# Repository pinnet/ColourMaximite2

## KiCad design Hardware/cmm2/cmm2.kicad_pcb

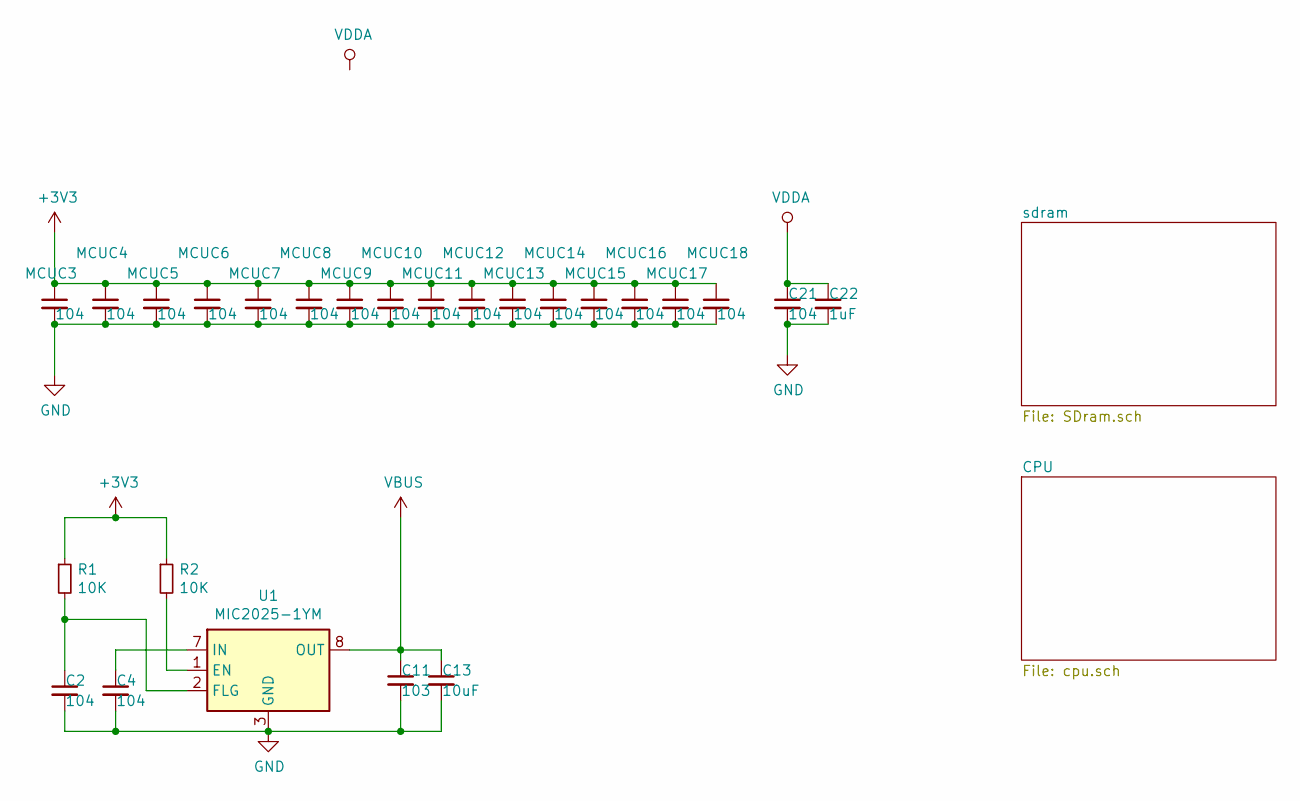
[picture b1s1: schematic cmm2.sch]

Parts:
C2, C4, C21: 104; C_0402_1005Metric
C11: 103; C_0402_1005Metric
C13: 10uF; C_0603_1608Metric
C22: 1uF; C_0402_1005Metric
MCUC3, MCUC4, MCUC5, MCUC6, MCUC7, MCUC8, MCUC9, MCUC10, MCUC11, MCUC12, MCUC13, MCUC14, MCUC15, MCUC16, MCUC17, MCUC18: 104; C_0402_1005Metric
R1, R2: 10K; R_0402_1005Metric
U1: MIC2025-1YM; SOIC-8_3.9x4.9mm_P1.27mm

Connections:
+3V3: MCUC3.1, MCUC4.1, MCUC5.1, MCUC6.1, MCUC7.1, MCUC8.1, MCUC9.1, MCUC10.1, MCUC11.1, MCUC12.1, MCUC13.1, MCUC14.1, MCUC15.1, MCUC16.1, MCUC17.1, MCUC18.1, R1.1, R2.1; also elsewhere on the board
GND: C2.2, C4.2, C11.2, C13.2, C21.2, C22.2, MCUC3.2, MCUC4.2, MCUC5.2, MCUC6.2, MCUC7.2, MCUC8.2, MCUC9.2, MCUC10.2, MCUC11.2, MCUC12.2, MCUC13.2, MCUC14.2, MCUC15.2, MCUC16.2, MCUC17.2, MCUC18.2, U1.3 (GND); also elsewhere on the board
unnamed: C2.1, R1.2, U1.2 (FLG)
unnamed: C4.1, U1.7 (IN)
unnamed: R2.2, U1.1 (EN)
VBUS: C11.1, C13.1, U1.6 (OUT), U1.8 (OUT)
VDDA: C21.1, C22.1; also elsewhere on the board

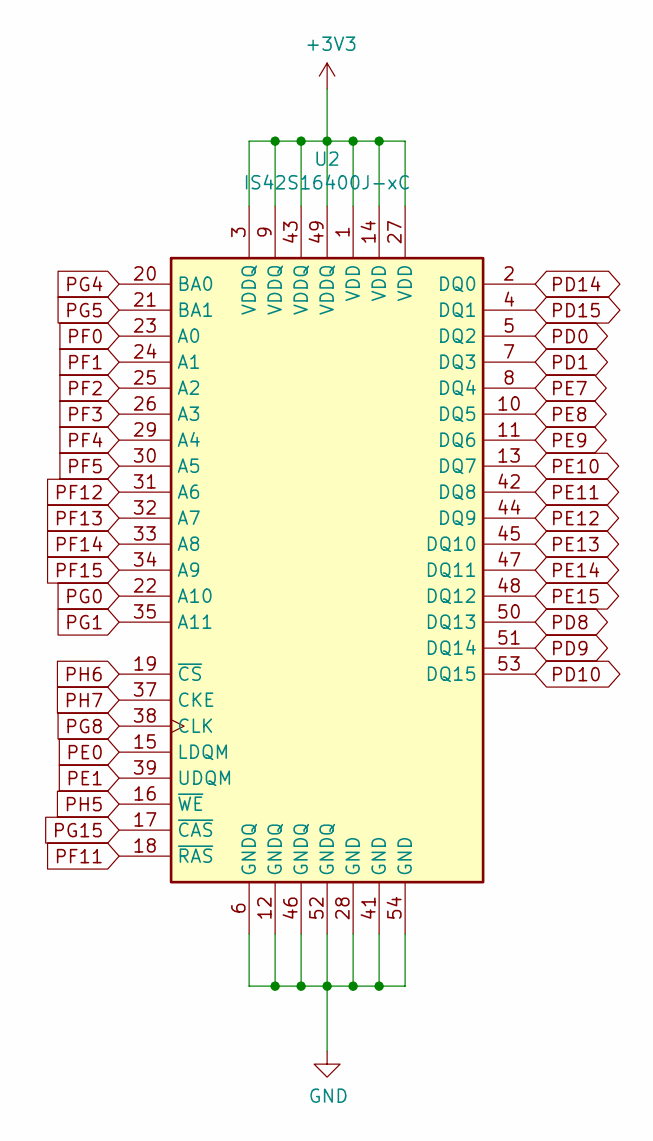
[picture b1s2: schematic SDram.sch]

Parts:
U2: IS42S16400J-xC; TSOP-II-54_22.2x10.16mm_P0.8mm

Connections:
+3V3: U2.1 (VDD), U2.3 (VDDQ), U2.9 (VDDQ), U2.14 (VDD), U2.27 (VDD), U2.43 (VDDQ), U2.49 (VDDQ); also elsewhere on the board
GND: U2.6 (GNDQ), U2.12 (GNDQ), U2.28 (GND), U2.41 (GND), U2.46 (GNDQ), U2.52 (GNDQ), U2.54 (GND); also elsewhere on the board
PD0: U2.5 (DQ2); also elsewhere on the board
PD1: U2.7 (DQ3); also elsewhere on the board
PD8: U2.50 (DQ13); also elsewhere on the board
PD9: U2.51 (DQ14); also elsewhere on the board
PD10: U2.53 (DQ15); also elsewhere on the board
PD14: U2.2 (DQ0); also elsewhere on the board
PD15: U2.4 (DQ1); also elsewhere on the board
PE0: U2.15 (LDQM); also elsewhere on the board
PE1: U2.39 (UDQM); also elsewhere on the board
PE7: U2.8 (DQ4); also elsewhere on the board
PE8: U2.10 (DQ5); also elsewhere on the board
PE9: U2.11 (DQ6); also elsewhere on the board
PE10: U2.13 (DQ7); also elsewhere on the board
PE11: U2.42 (DQ8); also elsewhere on the board
PE12: U2.44 (DQ9); also elsewhere on the board
PE13: U2.45 (DQ10); also elsewhere on the board
PE14: U2.47 (DQ11); also elsewhere on the board
PE15: U2.48 (DQ12); also elsewhere on the board
PF0: U2.23 (A0); also elsewhere on the board
PF1: U2.24 (A1); also elsewhere on the board
PF2: U2.25 (A2); also elsewhere on the board
PF3: U2.26 (A3); also elsewhere on the board
PF4: U2.29 (A4); also elsewhere on the board
PF5: U2.30 (A5); also elsewhere on the board
PF11: U2.18 (~RAS); also elsewhere on the board
PF12: U2.31 (A6); also elsewhere on the board
PF13: U2.32 (A7); also elsewhere on the board
PF14: U2.33 (A8); also elsewhere on the board
PF15: U2.34 (A9); also elsewhere on the board
PG0: U2.22 (A10); also elsewhere on the board
PG1: U2.35 (A11); also elsewhere on the board
PG4: U2.20 (BA0); also elsewhere on the board
PG5: U2.21 (BA1); also elsewhere on the board
PG8: U2.38 (CLK); also elsewhere on the board
PG15: U2.17 (~CAS); also elsewhere on the board
PH5: U2.16 (~WE); also elsewhere on the board
PH6: U2.19 (~CS); also elsewhere on the board
PH7: U2.37 (CKE); also elsewhere on the board

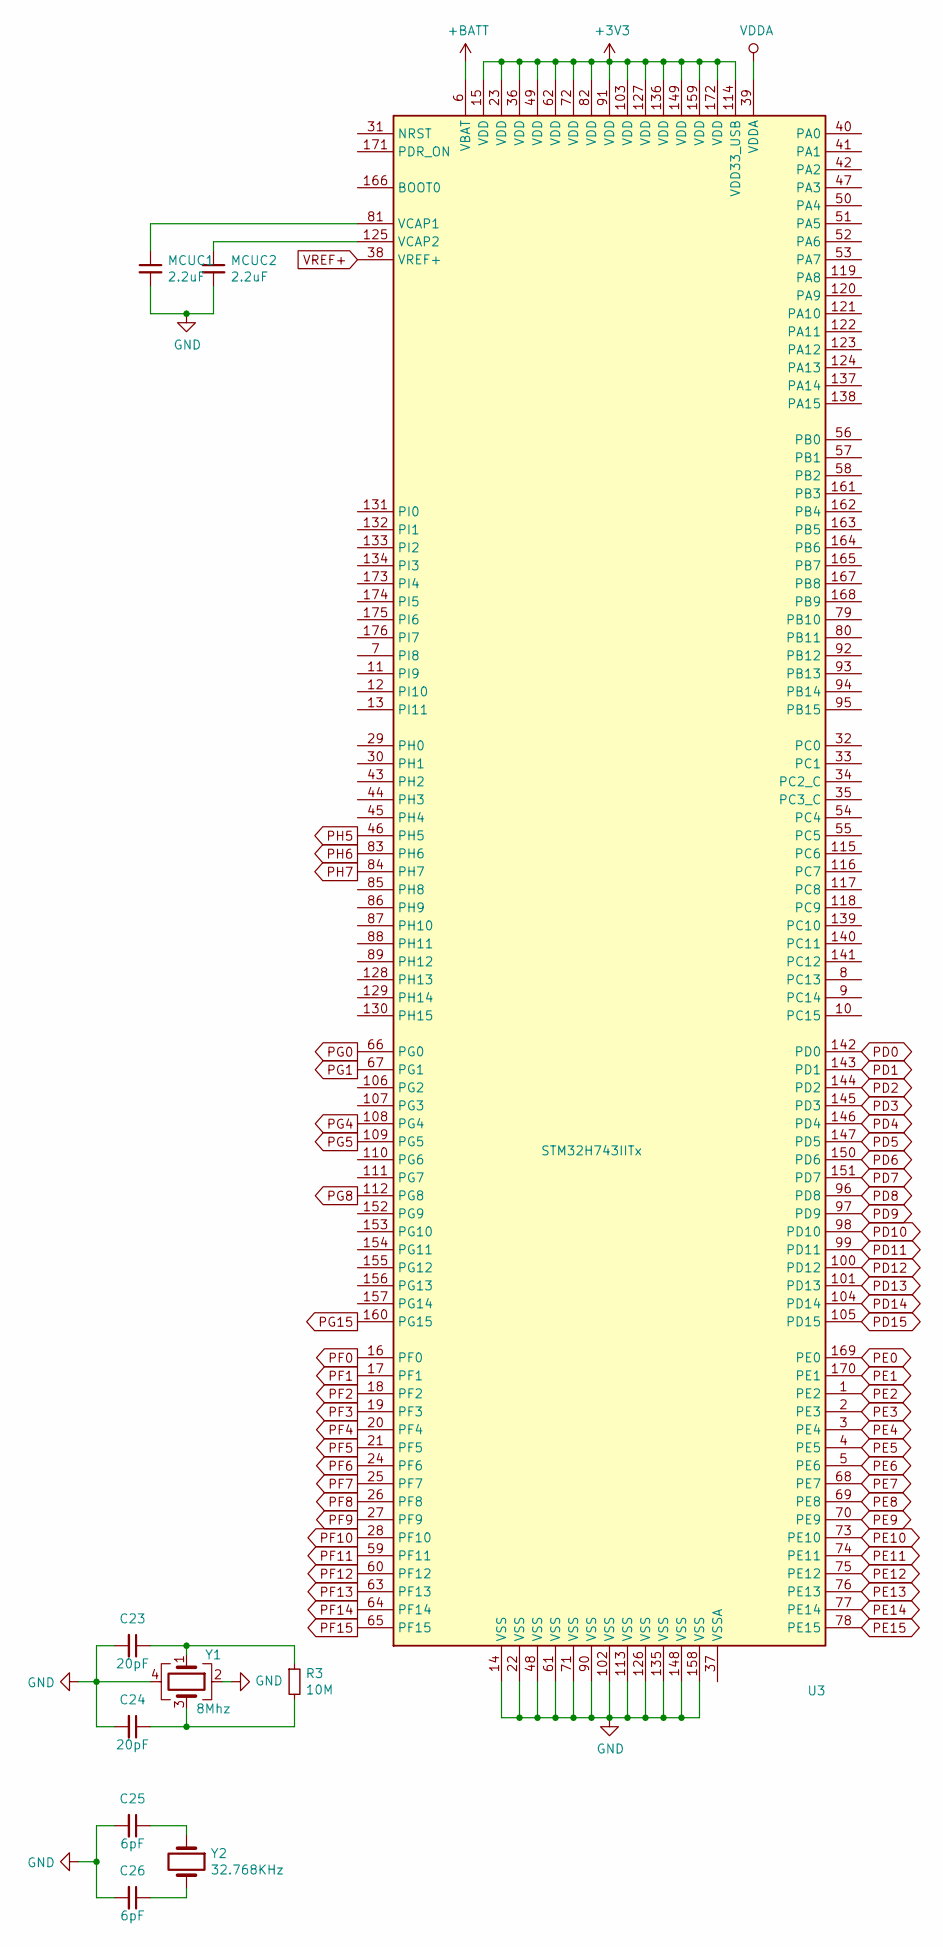
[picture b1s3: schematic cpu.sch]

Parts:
C23, C24: 20pF; C_0402_1005Metric
C25, C26: 6pF; C_0402_1005Metric
MCUC1, MCUC2: 2.2uF; C_0402_1005Metric
R3: 10M; R_0402_1005Metric
U3: STM32H743IITx; LQFP-176_24x24mm_P0.5mm
Y1: 8Mhz; Crystal_SMD_5032-4Pin_5.0x3.2mm
Y2: 32.768KHz; Crystal_SMD_3215-2Pin_3.2x1.5mm

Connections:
+3V3: U3.15 (VDD), U3.23 (VDD), U3.36 (VDD), U3.49 (VDD), U3.62 (VDD), U3.72 (VDD), U3.82 (VDD), U3.91 (VDD), U3.103 (VDD), U3.114 (VDD33_USB), U3.127 (VDD), U3.136 (VDD), U3.149 (VDD), U3.159 (VDD), U3.172 (VDD); also elsewhere on the board
+BATT: U3.6 (VBAT)
GND: C23.2, C24.2, C25.2, C26.2, MCUC1.2, MCUC2.2, U3.14 (VSS), U3.22 (VSS), U3.48 (VSS), U3.61 (VSS), U3.71 (VSS), U3.90 (VSS), U3.102 (VSS), U3.113 (VSS), U3.126 (VSS), U3.135 (VSS), U3.148 (VSS), U3.158 (VSS), Y1.2, Y1.4; also elsewhere on the board
unnamed: C23.1, R3.1, Y1.1
unnamed: C24.1, R3.2, Y1.3
unnamed: C25.1, Y2.1
unnamed: C26.1, Y2.2
unnamed: MCUC1.1, U3.81 (VCAP1)
unnamed: MCUC2.1, U3.125 (VCAP2)
PD0: U3.142 (PD0); also elsewhere on the board
PD1: U3.143 (PD1); also elsewhere on the board
PD2: U3.144 (PD2)
PD3: U3.145 (PD3)
PD4: U3.146 (PD4)
PD5: U3.147 (PD5)
PD6: U3.150 (PD6)
PD7: U3.151 (PD7)
PD8: U3.96 (PD8); also elsewhere on the board
PD9: U3.97 (PD9); also elsewhere on the board
PD10: U3.98 (PD10); also elsewhere on the board
PD11: U3.99 (PD11)
PD12: U3.100 (PD12)
PD13: U3.101 (PD13)
PD14: U3.104 (PD14); also elsewhere on the board
PD15: U3.105 (PD15); also elsewhere on the board
PE0: U3.169 (PE0); also elsewhere on the board
PE1: U3.170 (PE1); also elsewhere on the board
PE2: U3.1 (PE2)
PE3: U3.2 (PE3)
PE4: U3.3 (PE4)
PE5: U3.4 (PE5)
PE6: U3.5 (PE6)
PE7: U3.68 (PE7); also elsewhere on the board
PE8: U3.69 (PE8); also elsewhere on the board
PE9: U3.70 (PE9); also elsewhere on the board
PE10: U3.73 (PE10); also elsewhere on the board
PE11: U3.74 (PE11); also elsewhere on the board
PE12: U3.75 (PE12); also elsewhere on the board
PE13: U3.76 (PE13); also elsewhere on the board
PE14: U3.77 (PE14); also elsewhere on the board
PE15: U3.78 (PE15); also elsewhere on the board
PF0: U3.16 (PF0); also elsewhere on the board
PF1: U3.17 (PF1); also elsewhere on the board
PF2: U3.18 (PF2); also elsewhere on the board
PF3: U3.19 (PF3); also elsewhere on the board
PF4: U3.20 (PF4); also elsewhere on the board
PF5: U3.21 (PF5); also elsewhere on the board
PF6: U3.24 (PF6)
PF7: U3.25 (PF7)
PF8: U3.26 (PF8)
PF9: U3.27 (PF9)
PF10: U3.28 (PF10)
PF11: U3.59 (PF11); also elsewhere on the board
PF12: U3.60 (PF12); also elsewhere on the board
PF13: U3.63 (PF13); also elsewhere on the board
PF14: U3.64 (PF14); also elsewhere on the board
PF15: U3.65 (PF15); also elsewhere on the board
PG0: U3.66 (PG0); also elsewhere on the board
PG1: U3.67 (PG1); also elsewhere on the board
PG4: U3.108 (PG4); also elsewhere on the board
PG5: U3.109 (PG5); also elsewhere on the board
PG8: U3.112 (PG8); also elsewhere on the board
PG15: U3.160 (PG15); also elsewhere on the board
PH5: U3.46 (PH5); also elsewhere on the board
PH6: U3.83 (PH6); also elsewhere on the board
PH7: U3.84 (PH7); also elsewhere on the board
VDDA: U3.39 (VDDA); also elsewhere on the board
VREF+: U3.38 (VREF+)

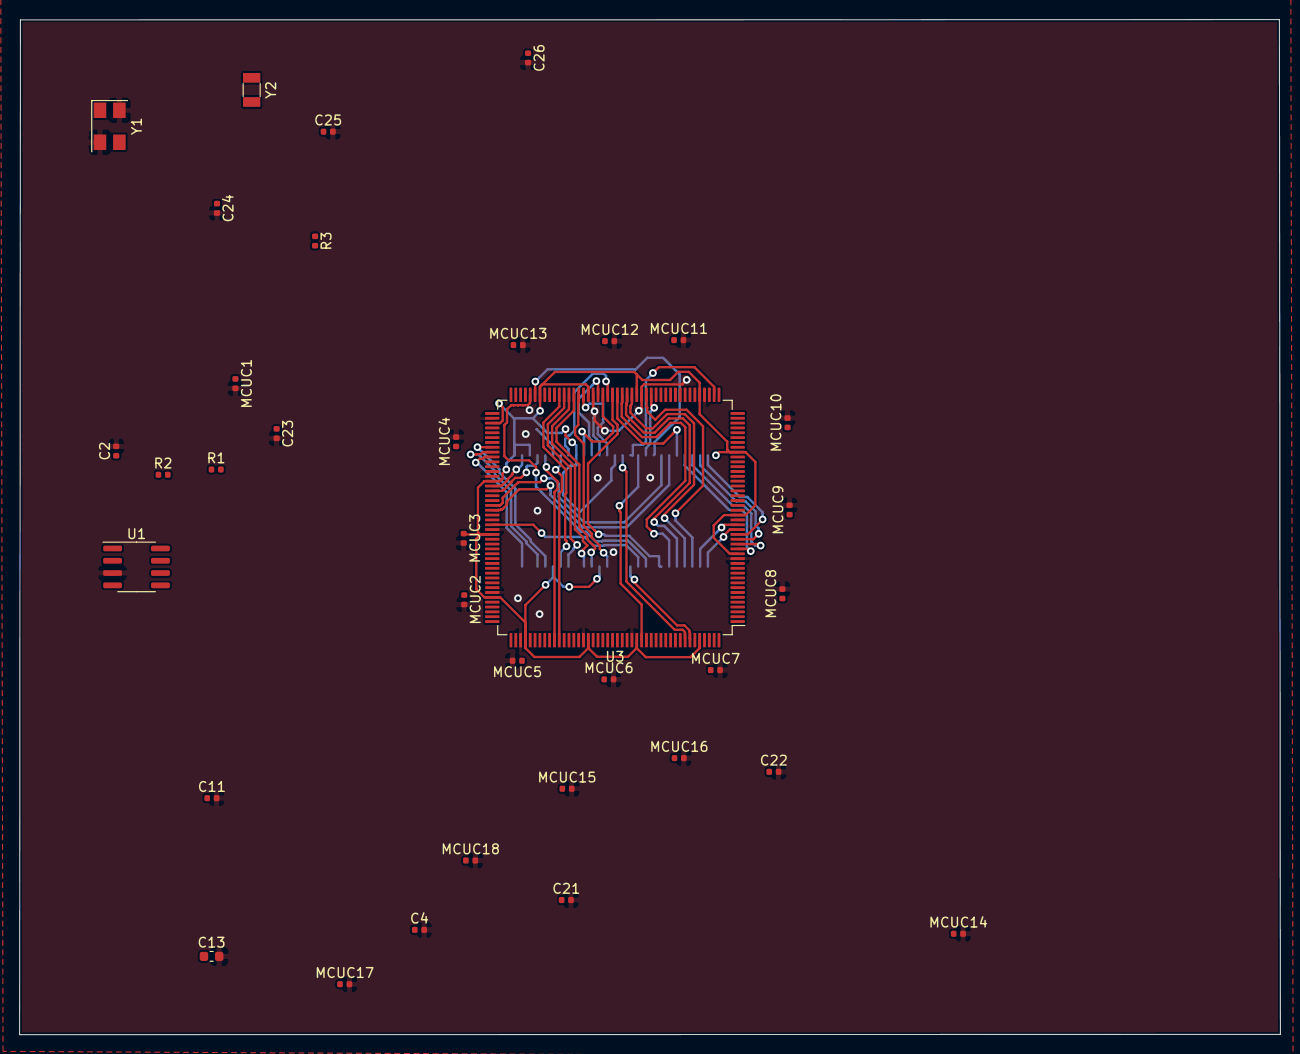
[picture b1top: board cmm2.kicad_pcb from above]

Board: 2 copper layers, 130.3 x 104.9 mm, 36 parts (1 on the bottom side), 51 nets.

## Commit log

2020-07-18 Inital commit
2020-07-26 Laest update
2020-07-26 latest update
